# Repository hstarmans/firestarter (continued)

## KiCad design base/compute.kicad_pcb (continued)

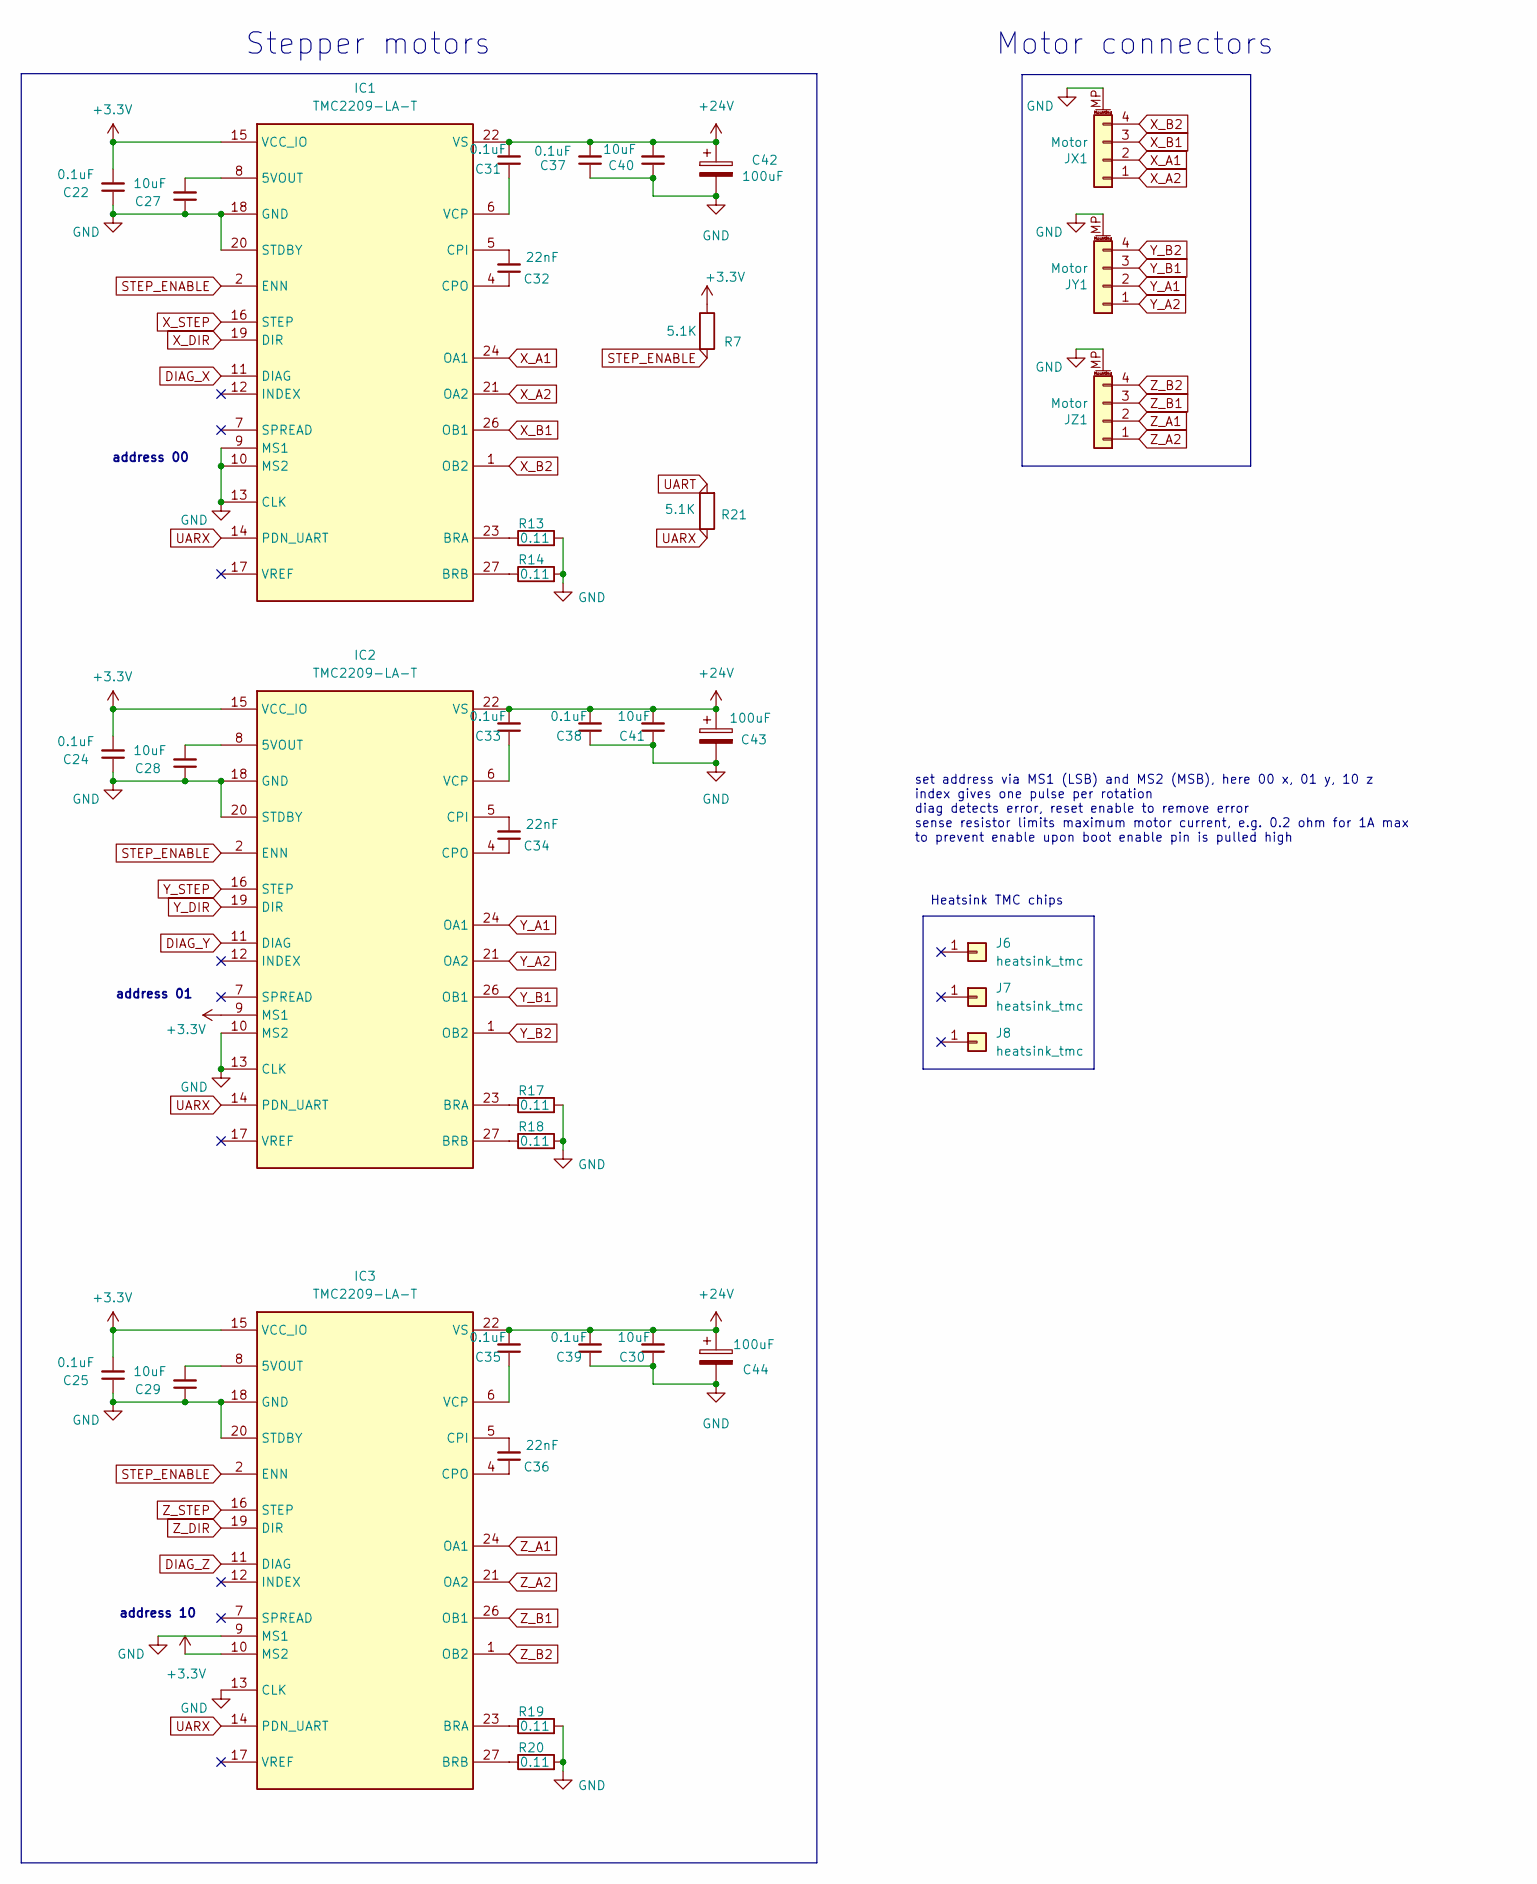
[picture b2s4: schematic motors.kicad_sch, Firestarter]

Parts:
C22, C24, C25, C31, C33, C35, C37, C38, C39: 0.1uF; C_0805_2012Metric_Pad1.18x1.45mm_HandSolder; mouser# 80-C0805C104J5R
C27, C28, C29, C30, C40, C41: 10uF; C_0805_2012Metric_Pad1.18x1.45mm_HandSolder; mouser# 81-GRM21BR61H106KE3L
C32, C34, C36: 22nF; C_0805_2012Metric_Pad1.18x1.45mm_HandSolder; mouser# 603-CC805KRX7R9BB222
C42, C43, C44: 100uF; CP_Elec_6.3x7.7; mouser# 647-UCD1V101MNL1GS; farnell# 4765491
IC1, IC2, IC3: TMC2209-LA-T; QFN50P500X500X90-29N-D; mouser# 700-TMC2209-LA-T; farnell# 3131535
J6, J7, J8: heatsink_tmc; mouser# 490-HSB01-080808
JX1: Motor; JST_XH_S4B-XH-SM4-TB_1x04-1MP_P2.50mm_Horizontal; mouser# 306-S4BXHSM4TBLFSN; farnell# 2399478
JY1: Motor; JST_XH_S4B-XH-SM4-TB_1x04-1MP_P2.50mm_Horizontal; mouser# 306-S4BXHSM4TBLFSN; farnell# 2399478
JZ1: Motor; JST_XH_S4B-XH-SM4-TB_1x04-1MP_P2.50mm_Horizontal; mouser# 306-S4BXHSM4TBLFSN; farnell# 2399478
R7: 5.1K; R_0805_2012Metric; mouser# -71-CRCW0805-5.1K-E3; farnell# 1469937
R13, R14, R17, R18, R19, R20: 0.11; R_1206_3216Metric; mouser# 71-WSL1206R1100FEA; farnell# 1107360
R21: 5.1K; R_0805_2012Metric; mouser# -71-CRCW0805-5.1K-E3

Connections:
+3.3V: C22.2, C24.2, C25.2, IC1.15 (VCC_IO), IC2.9 (MS1), IC2.15 (VCC_IO), IC3.10 (MS2), IC3.15 (VCC_IO), R7.1; also elsewhere on the board
+24V: C30.2, C31.2, C33.2, C35.2, C37.2, C38.2, C39.2, C40.2, C41.2, C42.1, C43.1, C44.1, IC1.22 (VS), IC1.28 (VS), IC2.22 (VS), IC2.28 (VS), IC3.22 (VS), IC3.28 (VS); also elsewhere on the board
DIAG_X: IC1.11 (DIAG); also elsewhere on the board
DIAG_Y: IC2.11 (DIAG); also elsewhere on the board
DIAG_Z: IC3.11 (DIAG); also elsewhere on the board
GND: C22.1, C24.1, C25.1, C27.1, C28.1, C29.1, C30.1, C37.1, C38.1, C39.1, C40.1, C41.1, C42.2, C43.2, C44.2, IC1.3 (GND), IC1.9 (MS1), IC1.10 (MS2), IC1.13 (CLK), IC1.18 (GND), IC1.20 (STDBY), IC1.25 (GND), IC1.29 (GND), IC2.3 (GND), IC2.10 (MS2), IC2.13 (CLK), IC2.18 (GND), IC2.20 (STDBY), IC2.25 (GND), IC2.29 (GND), IC3.3 (GND), IC3.9 (MS1), IC3.13 (CLK), IC3.18 (GND), IC3.20 (STDBY), IC3.25 (GND), IC3.29 (GND), JX1.MP (MountPin), JY1.MP (MountPin), JZ1.MP (MountPin), R13.2, R14.2, R17.2, R18.2, R19.2, R20.2; also elsewhere on the board
unnamed: C27.2, IC1.8 (5VOUT)
unnamed: IC1.23 (BRA), R13.1
unnamed: IC1.27 (BRB), R14.1
unnamed: C32.2, IC1.5 (CPI)
unnamed: C32.1, IC1.4 (CPO)
unnamed: C31.1, IC1.6 (VCP)
unnamed: C28.2, IC2.8 (5VOUT)
unnamed: IC2.23 (BRA), R17.1
unnamed: IC2.27 (BRB), R18.1
unnamed: C34.2, IC2.5 (CPI)
unnamed: C34.1, IC2.4 (CPO)
unnamed: C33.1, IC2.6 (VCP)
unnamed: C29.2, IC3.8 (5VOUT)
unnamed: IC3.23 (BRA), R19.1
unnamed: IC3.27 (BRB), R20.1
unnamed: C36.2, IC3.5 (CPI)
unnamed: C36.1, IC3.4 (CPO)
unnamed: C35.1, IC3.6 (VCP)
STEP_ENABLE: IC1.2 (ENN), IC2.2 (ENN), IC3.2 (ENN), R7.2; also elsewhere on the board
UART: R21.2; also elsewhere on the board
UARX: IC1.14 (PDN_UART), IC2.14 (PDN_UART), IC3.14 (PDN_UART), R21.1; also elsewhere on the board
X_A1: IC1.24 (OA1), JX1.2
X_A2: IC1.21 (OA2), JX1.1
X_B1: IC1.26 (OB1), JX1.3
X_B2: IC1.1 (OB2), JX1.4
X_DIR: IC1.19 (DIR); also elsewhere on the board
X_STEP: IC1.16 (STEP); also elsewhere on the board
Y_A1: IC2.24 (OA1), JY1.2
Y_A2: IC2.21 (OA2), JY1.1
Y_B1: IC2.26 (OB1), JY1.3
Y_B2: IC2.1 (OB2), JY1.4
Y_DIR: IC2.19 (DIR); also elsewhere on the board
Y_STEP: IC2.16 (STEP); also elsewhere on the board
Z_A1: IC3.24 (OA1), JZ1.2
Z_A2: IC3.21 (OA2), JZ1.1
Z_B1: IC3.26 (OB1), JZ1.3
Z_B2: IC3.1 (OB2), JZ1.4
Z_DIR: IC3.19 (DIR); also elsewhere on the board
Z_STEP: IC3.16 (STEP); also elsewhere on the board

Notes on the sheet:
set address via MS1 (LSB) and MS2 (MSB), here 00 x, 01 y, 10 z index gives one pulse per rotation diag detects error, reset enable to remove error sense resistor limits maximum motor current, e.g. 0.2 ohm for 1A max to prevent enable upon boot enable pin is pulled high
address 10
address 00
Heatsink TMC chips
address 01
Stepper motors
Motor connectors

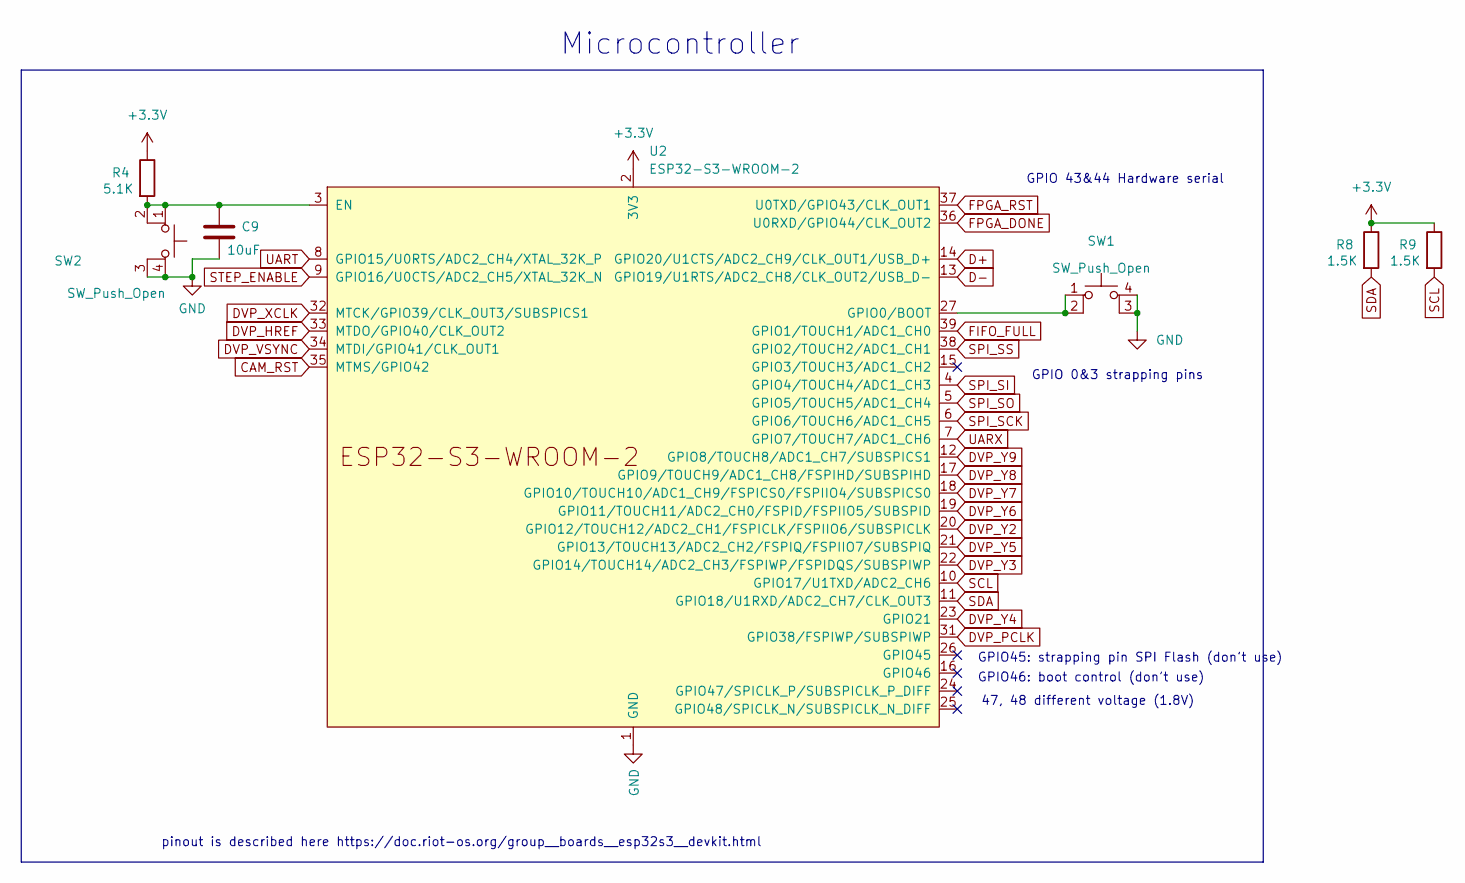
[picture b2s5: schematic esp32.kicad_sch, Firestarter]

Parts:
C9: 10uF; C_0805_2012Metric_Pad1.18x1.45mm_HandSolder; mouser# 81-GRM21BR61H106KE3L; farnell# 3790440
R4: 5.1K; R_0805_2012Metric; mouser# -71-CRCW0805-5.1K-E3; farnell# 1469937
R8, R9: 1.5K; R_0805_2012Metric; mouser# 652-CR0805JW-152ELF; farnell# 1469937
SW1, SW2: SW_Push_Open; SKRPABE010; mouser# 611-PTS810SJM250SMTR; farnell# 3261824
U2: ESP32-S3-WROOM-2; mouser# 356-SP32S3WM2N32R16V

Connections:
+3.3V: R4.1, R8.1, R9.1, U2.2 (3V3); also elsewhere on the board
CAM_RST: U2.35 (MTMS/GPIO42); also elsewhere on the board
D+: U2.14 (GPIO20/U1CTS/ADC2_CH9/CLK_OUT1/USB_D+); also elsewhere on the board
D-: U2.13 (GPIO19/U1RTS/ADC2_CH8/CLK_OUT2/USB_D-); also elsewhere on the board
DVP_HREF: U2.33 (MTDO/GPIO40/CLK_OUT2); also elsewhere on the board
DVP_PCLK: U2.31 (GPIO38/FSPIWP/SUBSPIWP); also elsewhere on the board
DVP_VSYNC: U2.34 (MTDI/GPIO41/CLK_OUT1); also elsewhere on the board
DVP_XCLK: U2.32 (MTCK/GPIO39/CLK_OUT3/SUBSPICS1); also elsewhere on the board
DVP_Y2: U2.20 (GPIO12/TOUCH12/ADC2_CH1/FSPICLK/FSPIIO6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); also elsewhere on the board
DVP_Y3: U2.22 (GPIO14/TOUCH14/ADC2_CH3/FSPIWP/FSPIDQS/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); also elsewhere on the board
DVP_Y4: U2.23 (GPIO21); also elsewhere on the board
DVP_Y5: U2.21 (GPIO13/TOUCH13/ADC2_CH2/FSPIQ/FSPIIO7/S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); also elsewhere on the board
DVP_Y6: U2.19 (GPIO11/TOUCH11/ADC2_CH0/FSPID/FSPIIO5/S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); also elsewhere on the board
DVP_Y7: U2.18 (GPIO10/TOUCH10/ADC1_CH9/FSPICS0/FSPIIO4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); also elsewhere on the board
DVP_Y8: U2.17 (GPIO9/TOUCH9/ADC1_CH8/FSPIHD/SUBSPIHD); also elsewhere on the board
DVP_Y9: U2.12 (GPIO8/TOUCH8/ADC1_CH7/SUBSPICS1); also elsewhere on the board
FIFO_FULL: U2.39 (GPIO1/TOUCH1/ADC1_CH0); also elsewhere on the board
FPGA_DONE: U2.36 (U0RXD/GPIO44/CLK_OUT2); also elsewhere on the board
FPGA_RST: U2.37 (U0TXD/GPIO43/CLK_OUT1); also elsewhere on the board
GND: C9.2, SW1.3 (K), SW1.4 (A), SW2.3 (K), SW2.4 (A), U2.1 (GND), U2.40 (GND), U2.41 (GND); also elsewhere on the board
unnamed: C9.1, R4.2, SW2.1, SW2.2, U2.3 (EN)
unnamed: SW1.1, SW1.2, U2.27 (GPIO0/BOOT)
SCL: R9.2, U2.10 (GPIO17/U1TXD/ADC2_CH6); also elsewhere on the board
SDA: R8.2, U2.11 (GPIO18/U1RXD/ADC2_CH7/CLK_OUT3); also elsewhere on the board
SPI_SCK: U2.6 (GPIO6/TOUCH6/ADC1_CH5); also elsewhere on the board
SPI_SI: U2.4 (GPIO4/TOUCH4/ADC1_CH3); also elsewhere on the board
SPI_SO: U2.5 (GPIO5/TOUCH5/ADC1_CH4); also elsewhere on the board
SPI_SS: U2.38 (GPIO2/TOUCH2/ADC1_CH1); also elsewhere on the board
STEP_ENABLE: U2.9 (GPIO16/U0CTS/ADC2_CH5/XTAL_32K_N); also elsewhere on the board
UART: U2.8 (GPIO15/U0RTS/ADC2_CH4/XTAL_32K_P); also elsewhere on the board
UARX: U2.7 (GPIO7/TOUCH7/ADC1_CH6); also elsewhere on the board

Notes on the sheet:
Microcontroller
GPIO 0&3 strapping pins
pinout is described here https://doc.riot-os.org/group__boards__esp32s3__devkit.html
GPIO45: strapping pin SPI Flash (don't use)
GPIO46: boot control (don't use)
GPIO 43&44 Hardware serial
47, 48 different voltage (1.8V)

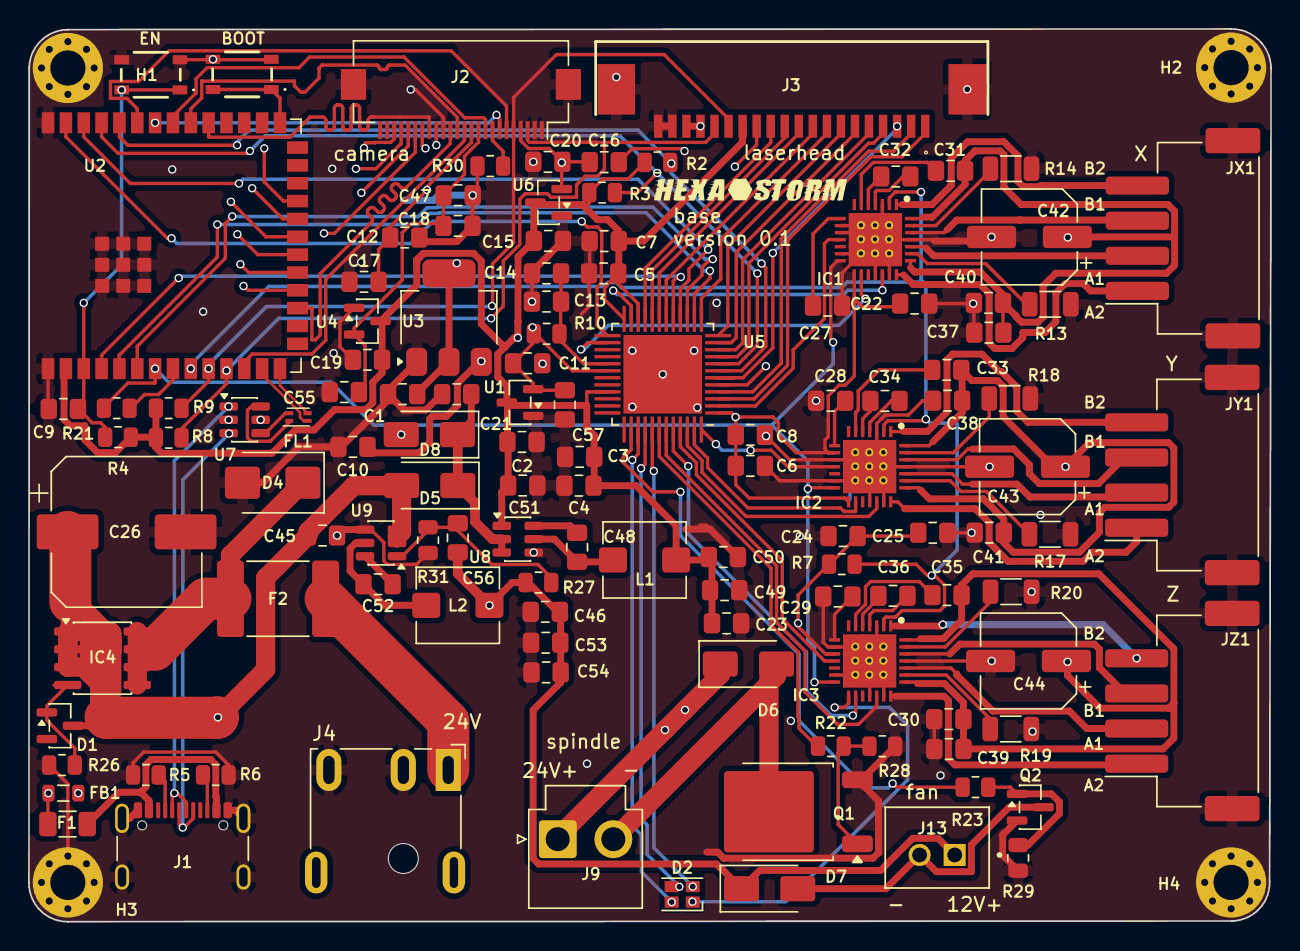
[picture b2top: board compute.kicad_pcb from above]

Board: 4 copper layers, 88.4 x 63.6 mm, 125 parts (0 on the bottom side), 117 nets.

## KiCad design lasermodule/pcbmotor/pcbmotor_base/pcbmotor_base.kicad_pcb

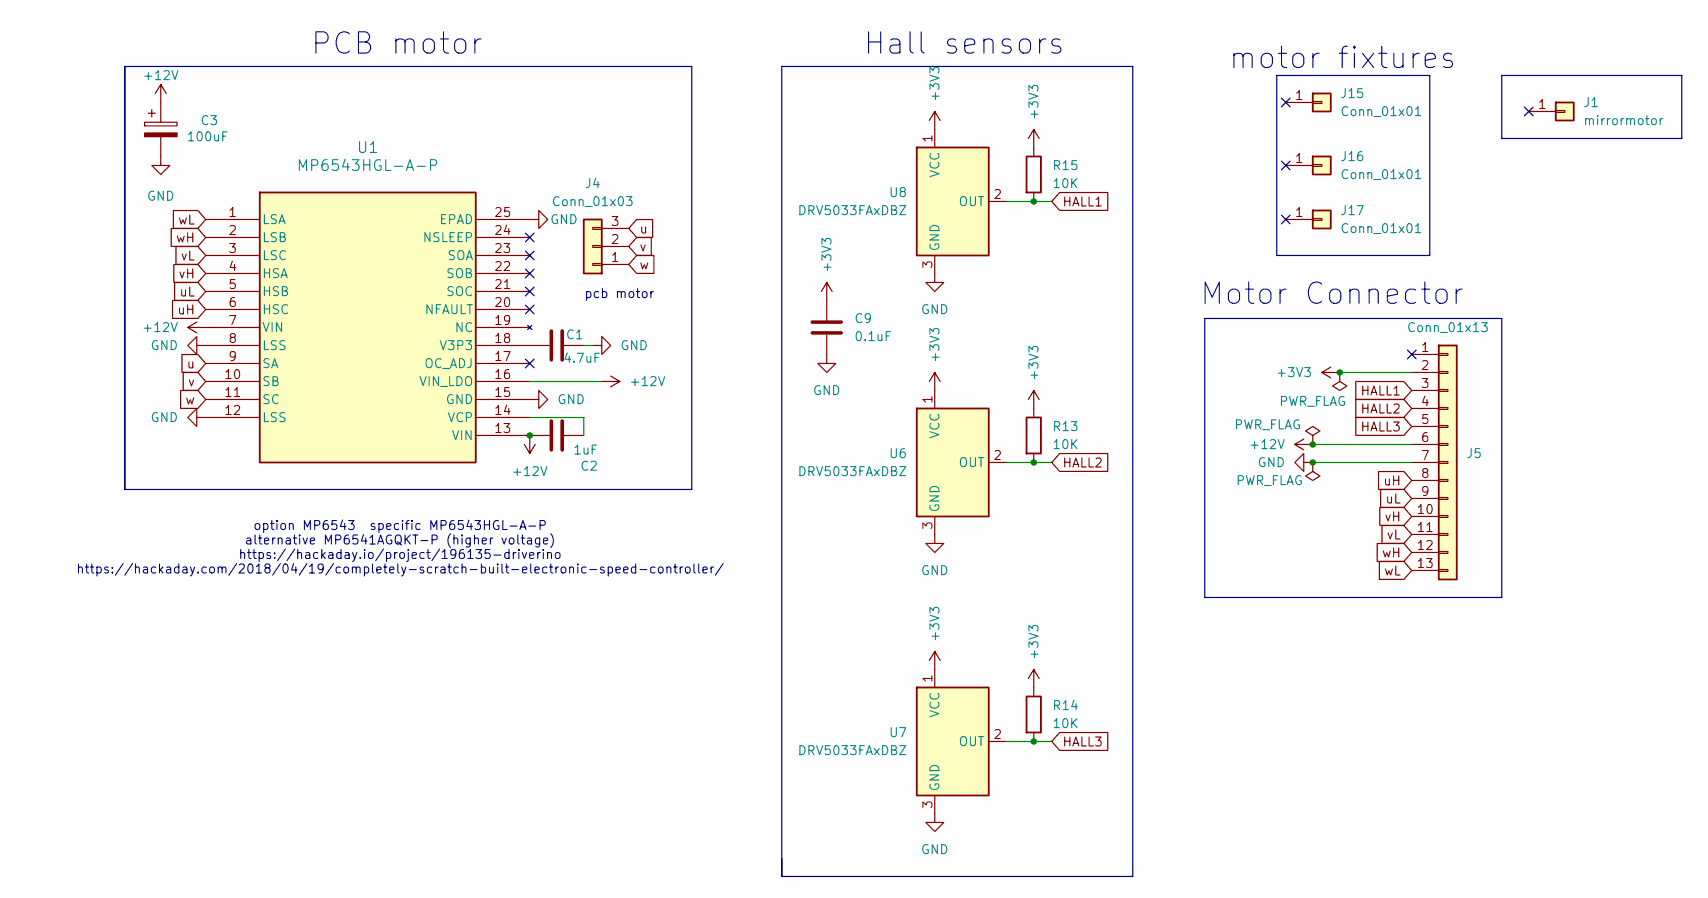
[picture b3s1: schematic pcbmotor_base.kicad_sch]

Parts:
C1: 4.7uF; C_0805_2012Metric; mouser# 81-GRM21BR61H475KE1L
C2: 1uF; C_0805_2012Metric; mouser# 581-08055C105KAT2A; farnell# 2094043
C3: 100uF; CP_Elec_6.3x5.4; mouser# 710-865080343009; farnell# 2466283
C9: 0.1uF; C_0805_2012Metric_Pad1.18x1.45mm_HandSolder; mouser# 80-C0805C104J5R
J1: mirrormotor; mirror_motor
J4: Conn_01x03; pcbmotor_smd
J5: Conn_01x13; motor_13pin
J15, J16, J17: Conn_01x01; TestPoint_Pad_D2.5mm_nosilk
R13, R14, R15: 10K; R_0805_2012Metric_Pad1.20x1.40mm_HandSolder; mouser# 71-CRCW080510K0JNEAC
U1: MP6543HGL-A-P; QFN-24-1EP_3x4mm_P0.4mm_EP1.65x2.65mm_ThermalVias; mouser# 946-MP6543HGL-A-P
U6, U7: DRV5033FAxDBZ; SOT-23; mouser# 595-RV5033FAEDBZRQ1
U8: DRV5033FAxDBZ; SOT-23; mouser# 595-RV5033FAEDBZRQ1; farnell# 3006067

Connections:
+3V3: C9.1, J5.2, R13.1, R14.1, R15.1, U6.1 (VCC), U7.1 (VCC), U8.1 (VCC)
+12V: C2.1, C3.1, J5.6, U1.7 (VIN), U1.13 (VIN), U1.16 (VIN_LDO)
GND: C1.1, C3.2, C9.2, J5.7, U1.8 (LSS), U1.12 (LSS), U1.15 (GND), U1.25 (EPAD), U6.3 (GND), U7.3 (GND), U8.3 (GND)
HALL1: J5.3, R15.2, U8.2 (OUT)
HALL2: J5.4, R13.2, U6.2 (OUT)
HALL3: J5.5, R14.2, U7.2 (OUT)
unnamed: C1.2, U1.18 (V3P3)
unnamed: C2.2, U1.14 (VCP)
u: J4.3, U1.9 (SA)
uH: J5.8, U1.6 (HSC)
uL: J5.9, U1.5 (HSB)
v: J4.2, U1.10 (SB)
vH: J5.10, U1.4 (HSA)
vL: J5.11, U1.3 (LSC)
w: J4.1, U1.11 (SC)
wH: J5.12, U1.2 (LSB)
wL: J5.13, U1.1 (LSA)

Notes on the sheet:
PCB motor
Motor Connector
Hall sensors
pcb motor
motor fixtures
option MP6543 specific MP6543HGL-A-P alternative MP6541AGQKT-P (higher voltage) https://hackaday.io/project/196135-driverino https://hackaday.com/2018/04/19/completely-scratch-built-electronic-speed-controller/

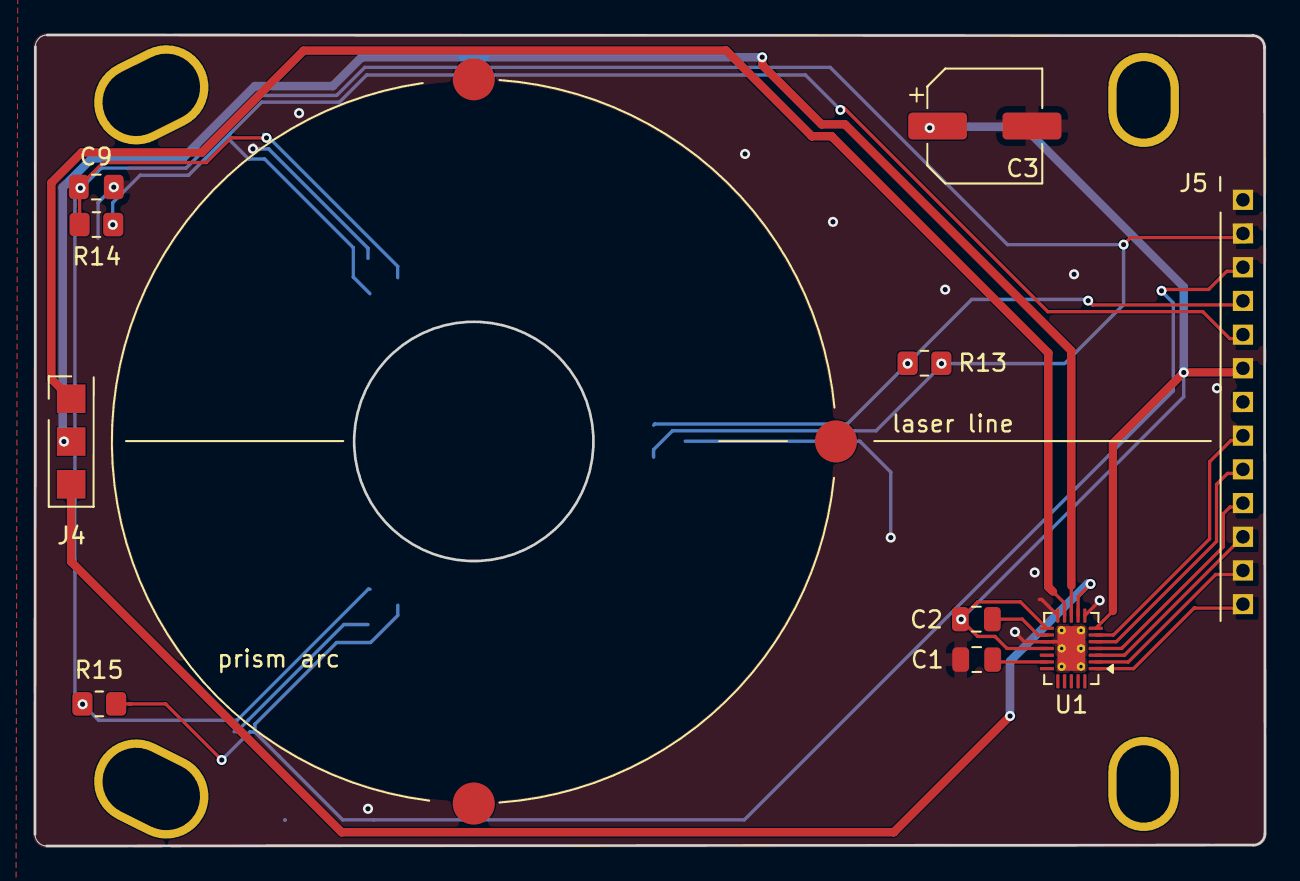
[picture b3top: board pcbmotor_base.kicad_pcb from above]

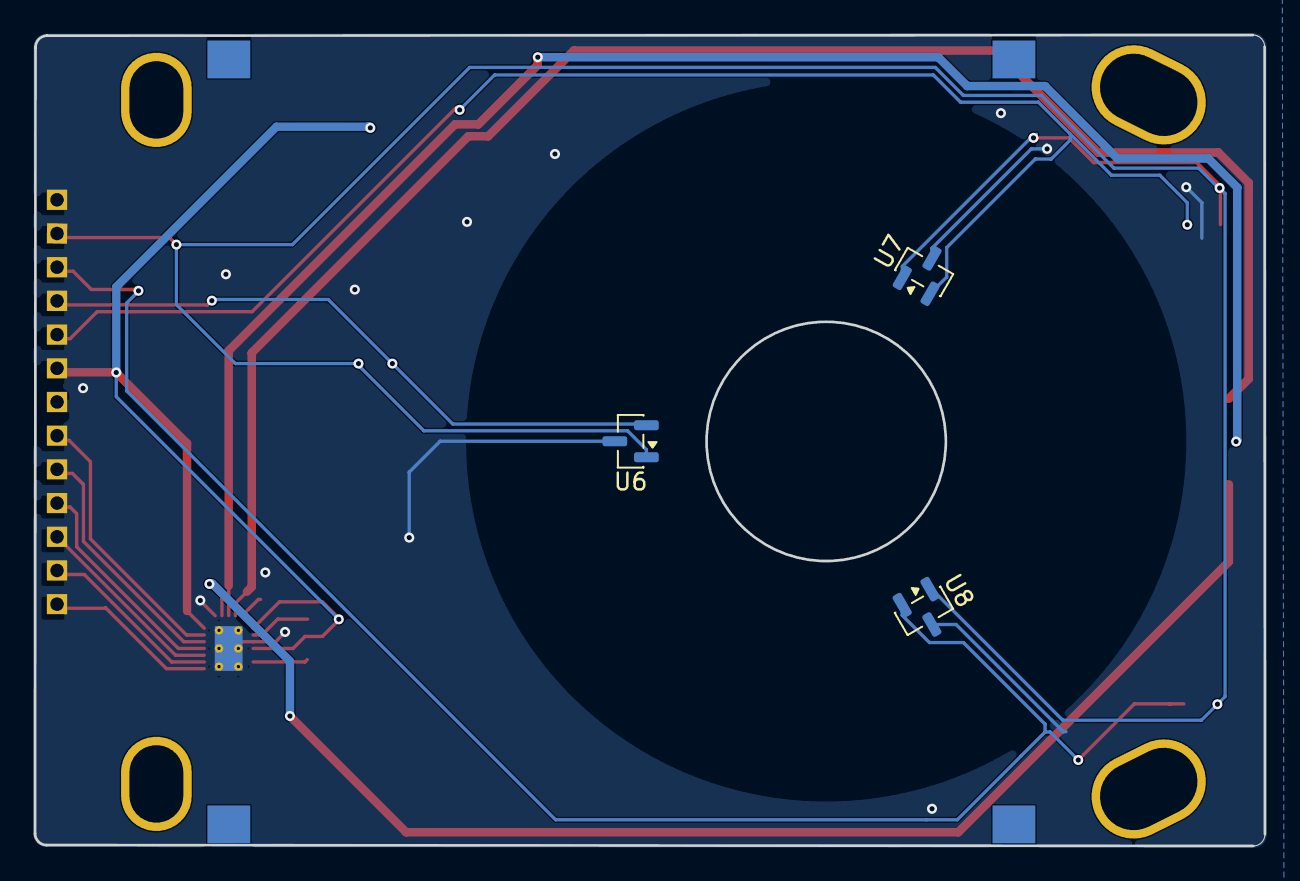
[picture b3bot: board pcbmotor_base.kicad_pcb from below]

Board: 2 copper layers, 73.0 x 48.1 mm, 17 parts (3 on the bottom side), 17 nets.

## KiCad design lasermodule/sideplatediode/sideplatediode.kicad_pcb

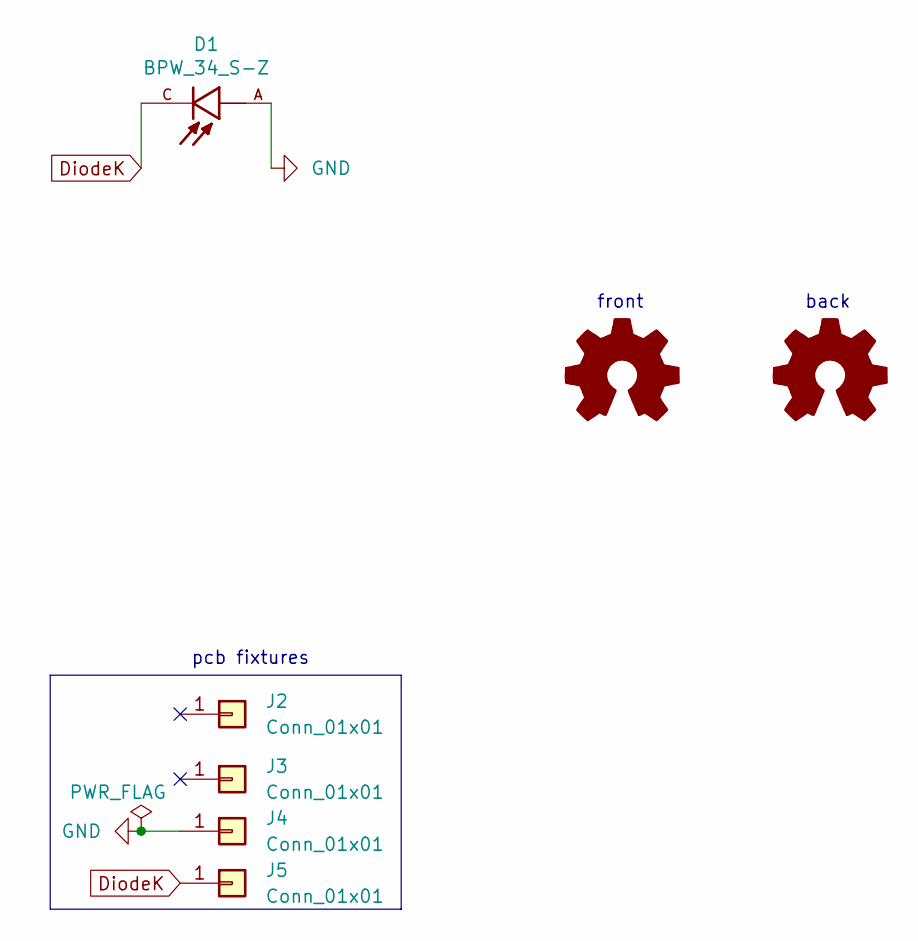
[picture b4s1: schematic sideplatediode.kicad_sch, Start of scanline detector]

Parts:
D1: BPW_34_S-Z; DIO_BPW_34_S-Z; manuf# BPW 34 S; mouser# 720-BPW34S-Z
J2, J3, J4, J5: Conn_01x01; TestPoint_Pad_2.0x2.0mm_nosilk
L1, L2: Logo_Open_Hardware_Small; hexastorm

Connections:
DiodeK: D1.C, J5.1 (Pin_1_1)
GND: D1.A, J4.1 (Pin_1_1)

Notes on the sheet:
back
pcb fixtures
front

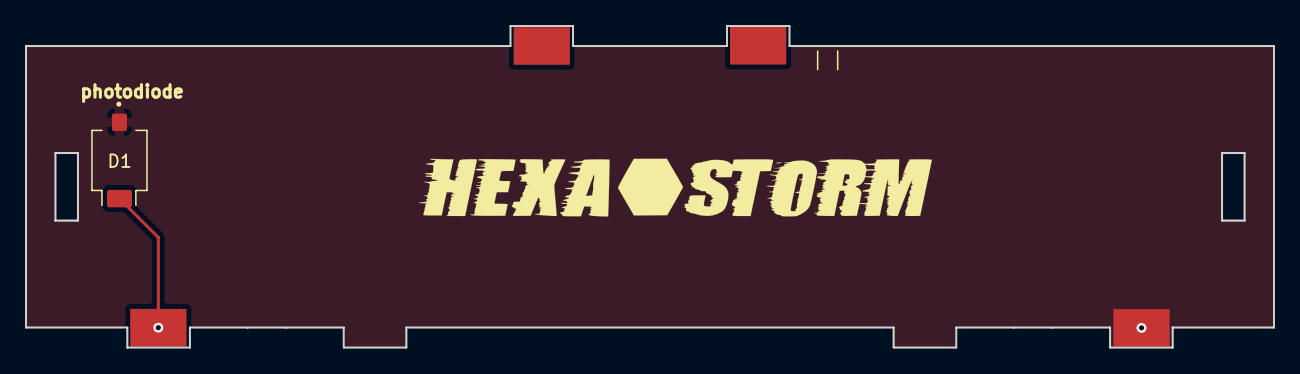
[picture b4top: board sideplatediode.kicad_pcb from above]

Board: 2 copper layers, 99.8 x 25.7 mm, 7 parts (1 on the bottom side), 2 nets.

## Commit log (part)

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2018-12-04 improved readme
    added notes for pcb
2018-12-04 added first sketch of board
2018-12-05 last commit was from old raspb pi trial, this is the new version for beaglebonee
2019-01-07 started with BOM
2019-01-08 added cap
2019-01-24 added some parts to bom and notes
2019-01-24 added some components
2019-03-07 some change
2019-03-07 extended notes
2019-03-08 added changes
2019-03-11 added more notes with respect to fet
2019-03-12 extended notes with hdmi, stepper tmc2130 spi connection
2019-03-13 proceeded with schematics, added most pins and layed out stepper motors
2019-03-19 added connectors
2019-03-20 added psu connection plus protection updated components list added library part for digipot and laserdiode driver
2019-03-20 update library file
2019-03-24 finalized schematic, added PWM for fan.
2019-03-25 updated components and links to datasheets
2019-03-27 added footprints resistors and molex connectors
2019-03-31 added more schematics for firestarter
2019-03-31 added tdfn
2019-03-31 omg lock file
2019-04-02 added footprint for ichkb and renamed other footprints
2019-04-04 added fuses
2019-04-08 finilazed schematics, removed some bugs and added footprint power connector
2019-04-13 annotated components and passed rule check
2019-04-13 added pad of max5935, started creating pcb
2019-04-13 improved organization components cape
2019-04-14 started organizing components for PCB layout
2019-04-15 fixed relative imports, started reorganizing pcb
2019-04-15 moved power connector into direction of ethernet port idea is that board is placed on male headers to create more space
2019-04-16 reorganized pcb and updated footprints
2019-04-17 started creating tracks
2019-04-17 added ground and power plane restored of 0, 5, 12, 24v connectors
2019-04-18 finished routing board....
    still need to final check, add some text and make crucial tracks wider
2019-04-19 added extra tracks to improve current throughput board moved components as some would collide according to spec still need to add reference markers
2019-04-23 footprint stepper motors was incorrect, this has been fixed
2019-04-23 added logo
2019-04-25 added status to readme
2019-04-25 added shematic
2019-04-25 added schema
    added quick overview of schema
2019-04-25 typo
2019-04-29 updated components and added approximate cost of three boards
2019-04-29 added details costs pcbs
2019-05-01 added more detailed cost notes
2019-05-06 added build notes and image board
2019-05-06 image of populated board
2019-05-14 extended readme
2019-05-14 typo fix
2019-05-16 spindle past test
2019-05-24 added link to hstarmans ldgraphy fork
2019-07-22 start of new pcb repository
2019-07-22 updated schematics
2019-07-22 added boms
2019-07-23 finished layout of all PCBs
2019-09-12 fixed xpo pin connection
2019-09-23 tried to fix components that couldn't be viewed on linux
2019-09-23 fixed library error
2019-09-26 updated status
2019-09-26 updated readme
    updated readme
2019-09-26 added readme with pictures
2019-09-26 added vector images for pcbs
2019-09-26 added schema
2019-09-26 added pcb for scanhead
2019-09-26 added beaglebone cape
2019-09-26 removed costs
2019-09-26 added costs
2019-09-26 fixed costs
2019-10-23 added pinout polygon motor
2019-10-24 added more details on caps
2019-10-29 opamp out of stock
2019-11-05 there is no cross talk
    cross talk existed due to bad soldering joint
2019-11-05 fixed quantity errors in bom
2020-04-23 started with developing fpga board for raspberry
2020-04-26 added more footprints to schema
2020-04-28 added more pins to shema
2020-05-02 daisy chained steppers
2020-05-03 updated bom and shematic with a couple of caps and resistors
2020-05-07 removed files which should not be tracked
2020-05-08 updated schematic, improved layout
2020-05-09 reorganization of components
2020-05-11 proceeded with routing
2020-05-13 continued routing, 3V and GND not fully connected
2020-05-14 finished routing
2020-05-14 simplified readme
2020-05-14 added readme
2020-05-14 added image
2020-06-23 improved pcb
    made pincompatible with icezero SPI ports
    simplified PCB, reduced capacitors and removed 3V creator
2020-06-23 updated status of board
2020-09-22 new version of board
2020-11-27 zero wrongly denoted
2020-11-29 added further possible improvement
2021-01-05 updated 3D renders
2021-01-05 latest changes
2021-07-18 changed most cables to flatex or jumper wire moved from 1 diode to 2 diodes added spi readout chip for photodiode photodiode is now surface mount
2021-07-19 added rended connector
2021-07-20 updated all boards
2021-07-28 updated bom
2021-07-30 decided to move to ice40up5k
    reasons cheaper chip, easier and has a DSP.
2021-08-02 new boards
2021-10-01 fixed orientation connector laserdiode connector to correct side
2021-10-04 added debugging info start of scanline detector
2021-10-06 positioned diode at edge
2021-10-08 new cryled footprint changed footprint FPGA to simply debug
2021-10-12 3V routed via flatex
2021-10-14 changes scanhead pcb
2021-10-14 added laser housing as pcb
2021-10-15 improved bom changed export settings
2021-11-25 added motor pcb
2021-11-25 added notes
2021-11-26 wijzigingen bord
2021-12-02 added script
2021-12-02 simplified code
2021-12-03 small fixes
2021-12-04 refactored code
2021-12-06 removed spiral
2021-12-28 pins wrongly denoted on schematic
2022-01-03 nieuwe ideeen as
2022-01-10 added esp32 shield
2022-01-11 routed esp32 board
2022-01-12 adapted motor and ESP32 shield
2022-01-12 updated ESP32 shield
2022-01-12 updated shield
2022-01-28 moved to kicad 6 and added bom for ESP32 shield
2022-02-23 started with compact for version of laserhead
2022-02-24 updated compact scanhead
2022-02-25 updated model
2022-03-04 updated boards
2022-03-08 routed new boards for compact scanhead
2022-03-09 added two holes, rerouted board
2022-06-15 added design of june
2023-04-29 cleaned up repo for new design cycle
2023-05-03 laid out board
2023-05-08 finished schema for main
2023-05-08 remove
2023-05-09 added pcbmotor, renamed some folders
2023-05-09 removed motor
2023-05-11 further cleaned up and tested renders in blender
2023-05-11 started adding other plates
2023-06-06 synced latest changes
2023-06-10 simplified loading in freecad, updated pcbs
2023-06-11 pcbs can be rendered
2023-06-16 changed position logos
2023-09-22 added optimized pcbmotor of atomic14
2023-09-27 removed need for screws using pcb pads
2023-09-28 improved tracks
2023-10-08 started adding main board
2023-10-12 last save computer battery low
2023-10-12 flatex cable increased from 15 to 20 pins
2023-10-17 started routing main board with esp32
2023-10-20 finished routing main_board
2023-12-10 added some notes on detected issues
2024-01-24 started changing main board
2024-01-24 added reason for changes to main board
2024-02-14 updated step models
2024-02-15 routed main board
2024-02-16 updated design
2024-02-16 added render
2024-07-26 adding compute remove other components
2024-08-04 compute module ready for fab
2024-08-07 changes for extension
2024-08-12 modified extension
2024-08-13 improved layout main board
2024-08-18 moved from 2 headers to 1 smt 40 pin header
2024-08-22 moved stepper drivers to board, added smt connection for compute
2024-08-28 retracking board
2024-09-06 added git lfs, model for polygon mirror motor
2024-09-06 changed license
2024-10-02 base supports both PCB and mirror motor
2024-10-24 board almost fully synced close for release
2024-10-28 kicost integration for compute and extension
2024-10-28 improved position esp32, kicost integration fix for compute module
2024-10-28 added kicost tracking other plates, fixed plates
2024-10-30 added new driver for pcb motor
2024-10-31 fixed boms, small modifications to the boards.
2024-11-03 improved connection between pcb motor and base plate
2024-11-03 improved description
2024-11-07 changed colors of the plates
2024-11-15 added pcb files, added offset between compute and extension
2024-11-17 fixed typo, added standoff lasermodule
2024-11-20 added mount felixprinter, standoffs
2024-11-22 changes to reduce prices pcbway
2024-11-25 sent to pcbway
2024-12-14 fixes some mistake in the bom found in first assembly
2025-01-26 fixed issues uncovered with extension module
2025-01-26 improved readme
2025-01-26 fixed headers, shifted text base board
2025-01-27 added kicost notes
2025-01-29 fixed pullups i2c
2026-04-08 compute board 4 layer, with camera connector and small bug fixes
2026-04-10 schema extension finished, pre merge
2026-04-16 quick backup, decided to merge compute and extension
2026-04-26 schema support spindle, fan , 24V, compliant with VEVOR
2026-04-30 board passes all tests
2026-05-05 improved powernet, fixed bugs, tuned tracks for camera
2026-05-06 send to fab
2026-05-26 fixed: uartx res to 5.1K, switch connection cross, camera connextor top side
